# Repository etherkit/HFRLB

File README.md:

HFRLB
=====

An HF Return Loss Bridge for your measurement needs.

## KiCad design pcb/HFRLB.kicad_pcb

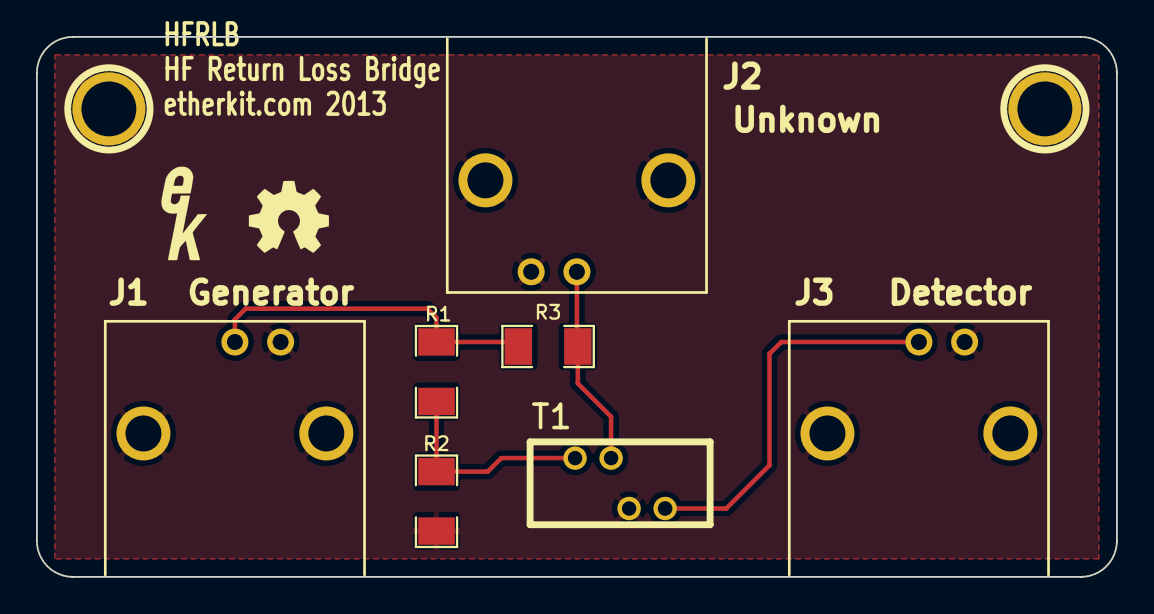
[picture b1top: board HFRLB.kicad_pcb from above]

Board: 2 copper layers, 60.0 x 30.0 mm, 10 parts (0 on the bottom side), 5 nets.

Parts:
1PIN, 1PIN#2: P***; 1pin
J1: Generator; BNC-AMPHENOL-31-5431-10RFX
J2: Unknown; BNC-AMPHENOL-31-5431-10RFX
J3: Detector; BNC-AMPHENOL-31-5431-10RFX
R1, R2, R3: 49.9 0.1%; SM1206
Ref**: Val**; EtherkitLogoSmall
T1: FB73-2401 10T bifilar; T37-V-BIFILARXFMR

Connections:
GND: 1PIN.1, 1PIN#2.1, J1.2, J2.2, J3.2, R2.2, T1.2
unnamed: J1.1, R1.1, R3.1
unnamed: R1.2, R2.1, T1.1
unnamed: J2.1, R3.2, T1.3
unnamed: J3.1, T1.4

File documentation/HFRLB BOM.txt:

HFRLB BOM
Etherkit
8 Sep 2013

| Part (marking)                  | Qty  | Ref                            | P/N
======================================================================================================
| BNC                               3      J1, J2, J3                       Amphenol 31-5431-10RFX

Resistors (all resistors 0.25 watt 1206 0.1%)
| 49.9                              3      R1, R2, R3                       Vishay TNPW120649R9BEEA

Miscellaneous
| Red Magnet Wire, 32 AWG (feet)    1
| Green Magnet Wire, 32 AWG (feet)  1
| PCB                               1
| Enclosure                         1

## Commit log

2013-09-09 Add README

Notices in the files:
pcb/HFRLB.kicad_pcb:
Creative Commons License CC-BY-SA
